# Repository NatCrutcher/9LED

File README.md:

## Overview

This is a small test PCB to experiment with wide color gamut LEDs. The initial plan is to use the following LEDs, driven by the TI TLC5971 (high-quality 16-bit PWM).

1. Violet 410 (XE-G)
2. Blue PC 460 (OSLON)
3. Cyan 500 (XE-G)
4. Green 525 (OSLON)
5. Yellow PC 590 (OSLON)
6. Red 620 (OSLON)
7. Photo Red 660 (XE-G)
8. Far Red 735 (Luxeon)
9. White (OSLON)

This should allow tests to compare more traditional RGB and RGBW color gamuts to wider gamuts. In particular, deeper reds, violet, and cyan. 

### Cyan
Initial testing shows that the cyan LED makes a color that is perceptually different from just mixing various amounts of green and blue. Green+blue results in the traditional computer monitor "cyan", which is really more turquoise. The pure cyan LED results in a more saturated (computer monitor cyan is a bit pastel by comparison) strong green-blue color.

### Violet

By itself, the violet LED is not what I expected: it seems almost like a purple/blue/white mixture. I need to do more research to make sure it is not exciting the phosphors in the white LED (perhaps build a board without the white). My plans are to compare purples (red+blue and red+violet) to see if violet generates noticeably different (i.e. more intense) purpl

### Photo Red and Far Red

This is an interesting example of how our eyes acclimate, color balance, and otherwise shift our perceptions. When I look at the normal red LED, it looks strongly red. But when I look at normal red next to photo red, the photo red looks more intensely red and the normal red starts to look like an orange-red. I want to try a larger experiment to determine how this effect scales.

The far red appears to be useless for LED sculptures, animations, or lighting. The perceived brightness is MUCH (like 10-20X) lower, so it can only produce very dim illumination. And as seen on the chromaticity diagrams, the perceived color is very close to photo red, so it does not meaningfully increase the gamut.

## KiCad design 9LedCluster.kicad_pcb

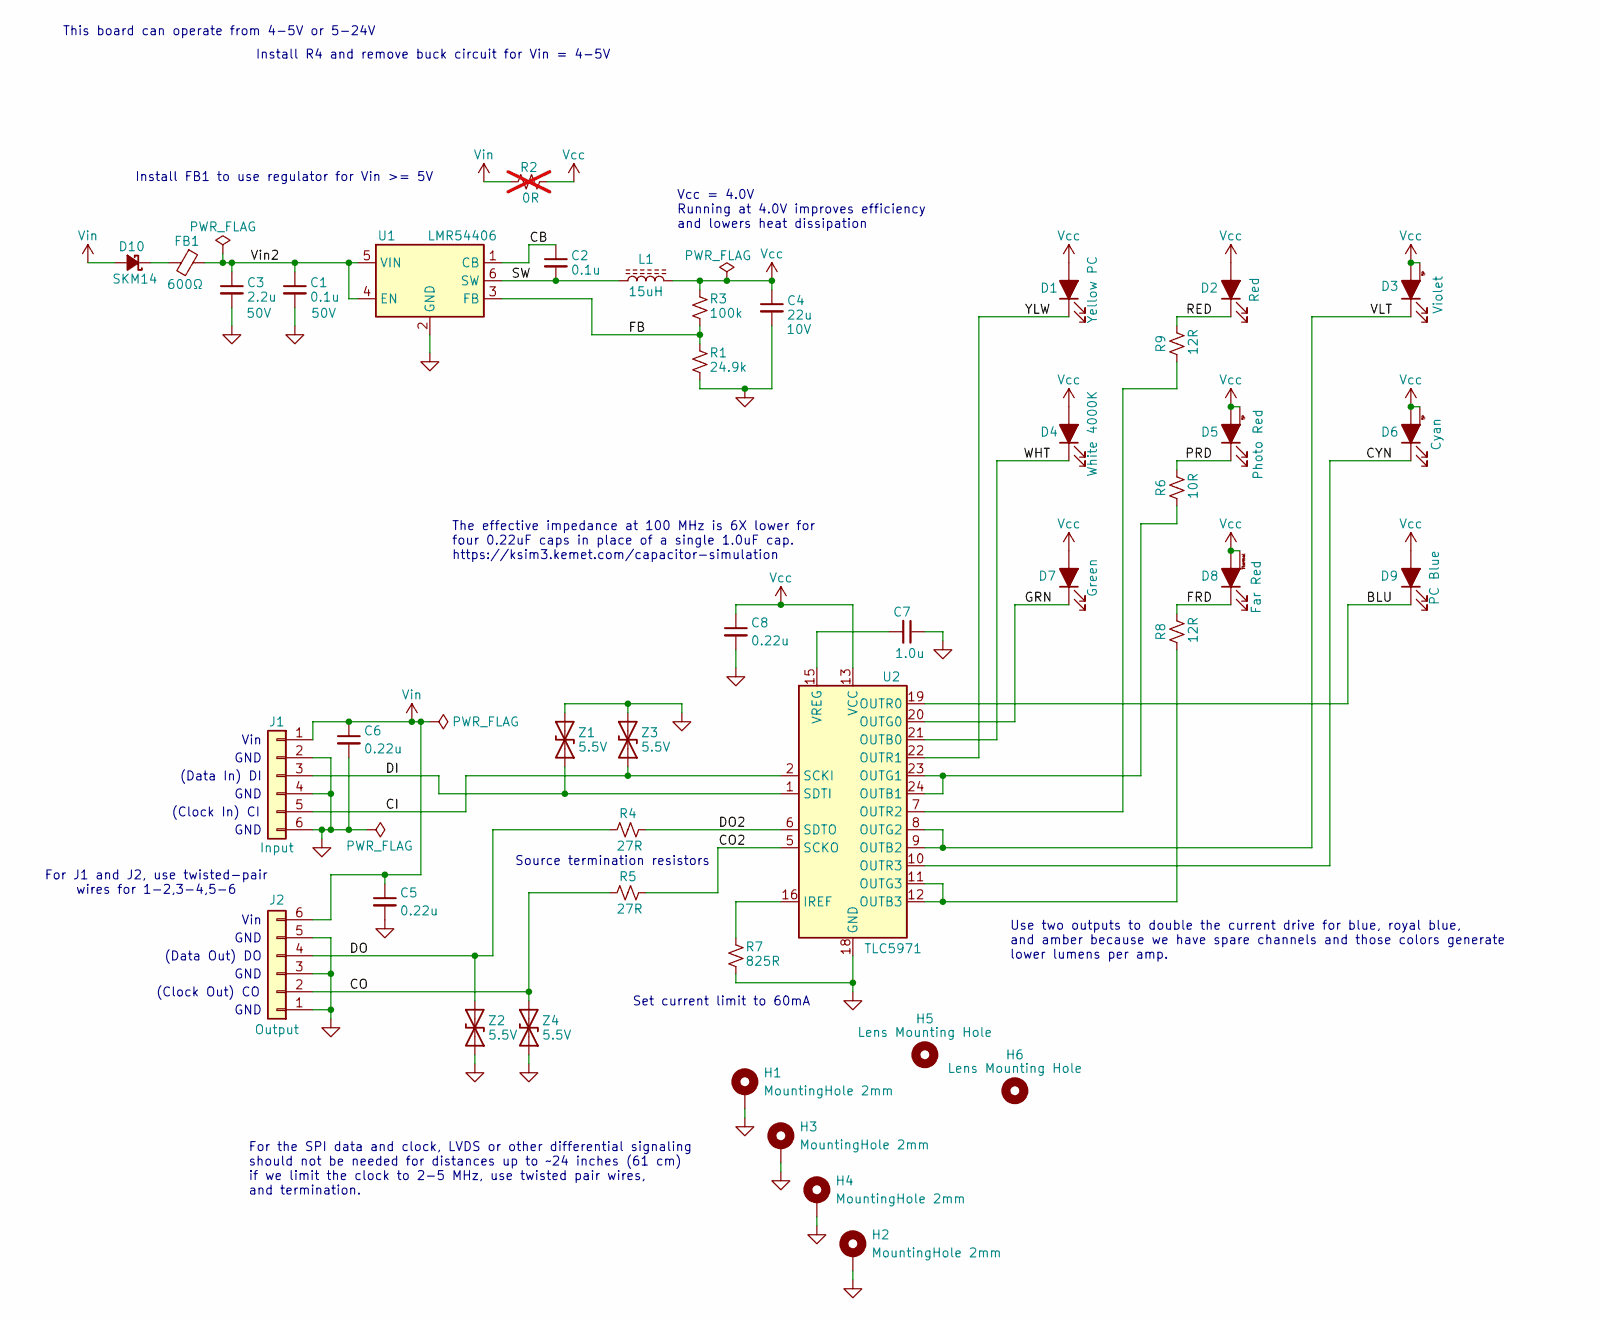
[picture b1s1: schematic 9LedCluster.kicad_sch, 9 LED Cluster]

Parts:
C1, C2: 0.1u; C_0402_1005Metric; Rating 50V; Tolerance 10%; MPN GRM155R71H104KE14D
C3: 2.2u; C_0805_2012Metric; Rating 50V; Tolerance 10%; MPN UMK212BB7225KG-T
C4: 22u; C_0805_2012Metric; Rating 10V; Tolerance 20%; MPN GRM21BZ71A226ME15L
C5, C6, C8: 0.22u; C_0402_1005Metric; Rating 16V; Tolerance 20%; MPN C0402C224M4RACTU
C7: 1.0u; C_0603_1608Metric; Rating 25V; Tolerance 10%; MPN TMK107B7105KA-T
D1: Yellow PC; OSRAM-OSLON-Pure-1414; Rating 350mA; MPN GY VJLPL1.F3-KULQ-YCYK-1
D2: Red; OSRAM-OSLON-Pure-1414; Rating 350mA; MPN GR VJLPL1.23-KQKS-A4R2-1
D3: Violet; Cree_XE-G; Rating 1A; MPN XEGAVT-H0-0000-000-000000K2001
D4: White 4000K; OSRAM-OSLON-Pure-1414; Rating 350mA; MPN GW VJLPL1.CM-K3LX-XX55-1
D5: Photo Red; Cree_XE-G; Rating 1A; MPN XEGAHR-H2-0000-000-000000H6001
D6: Cyan; Cree_XE-G; Rating 1A; MPN XEGACY-H2-0000-000-000000T3001
D7: Green; OSRAM-OSLON-Pure-1414; Rating 350mA; MPN GT VJLPL1.13-LPLS-T3T4-1
D8: Far Red; Luxeon_CZ_LED_AK; Rating 350mA; MPN L1C1-FRD1000000000
D9: PC Blue; OSRAM-OSLON-Pure-1414; Rating 350mA; MPN GB VJLPL1.F3-JRJT-BABB-1
D10: SKM14; D_SOD-123F; Rating 40V, 1A; Rating2 350mV @ 1A; MPN SKM14
FB1: 600Ω; R_0603_1608Metric_Pad0.98x0.95mm_HandSolder; Rating 1.3A; Rating2 DCR=150mΩ; MPN BLM18KG601SN1D
H1, H2, H3, H4: MountingHole 2mm; MountingHole_2.0mm_A
H5, H6: Lens Mounting Hole; MountingHole_2.0mm_NP
J1: Input; Conn_2.00mm_6_LED
J2: Output; Conn_2.00mm_6_LED
L1: 15uH; L_1210_3225Metric; Rating I=1.47; Rating2 320 mOhm Max; MPN BCL322520RT-150M-D
R1: 24.9k; R_0603_1608Metric; Tolerance 0.5%; Rating 0.063W; MPN RR0816P-2492-D-39C
R2: 0R; R_0402_1005Metric; Tolerance jumper; MPN RK73Z1ETTP; not fitted
R3: 100k; R_0603_1608Metric; Tolerance 0.5%; Rating 0.1W; MPN RT0603DRD07100KL
R4, R5: 27R; R_0402_1005Metric; Tolerance 1%; Rating 0.063W; MPN RT0402FRE0727RL
R6: 10R; R_0603_1608Metric; Tolerance 1%; Rating 0.125W; MPN RK73H1JTTD10R0F
R7: 825R; R_0402_1005Metric; Tolerance 1%; Rating 0.063W; MPN RR0510P-8250-D
R8, R9: 12R; R_0603_1608Metric; Tolerance 1%; Rating 0.125W; MPN RK73H1JTTD12R0F
U1: LMR54406; SOT-23-6; Rating 1.1MHz; Rating2 600mA; MPN LMR54406DBVR
U2: TLC5971; Texas_RGE0024H_VQFN-24-1EP_4x4mm_P0.5mm_EP2.7x2.7mm_Thermal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; Rating 17V, 60mA; Rating2 12ch, 16bit; MPN TLC5971RGER
Z1, Z2, Z3, Z4: 5.5V; R_0402_1005Metric; Rating 5.5V, 10pF; Rating2 25kV ESD; MPN GG040205100N2P

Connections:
/BLU: D9.K, U2.19 (OUTR0)
/CB: C2.1, U1.1 (CB)
/CI: J1.5, U2.2 (SCKI), Z3.1 (A1)
/CO: J2.2, R5.1, Z4.2 (A2)
/CO2: R5.2, U2.5 (SCKO)
/CYN: D6.K, U2.10 (OUTR3)
/DI: J1.3, U2.1 (SDTI), Z1.1 (A1)
/DO: J2.4, R4.1, Z2.2 (A2)
/DO2: R4.2, U2.6 (SDTO)
/FB: R1.1, R3.2, U1.3 (FB)
/FRD: D8.K, R8.2
/GRN: D7.K, U2.20 (OUTG0)
/PRD: D5.K, R6.2
/RED: D2.K, R9.2
/SW: C2.2, L1.1, U1.6 (SW)
/VLT: D3.K, U2.8 (OUTG2), U2.9 (OUTB2)
/Vin2: C1.1, C3.1, FB1.1, U1.4 (EN), U1.5 (VIN)
/WHT: D4.K, U2.21 (OUTB0)
/YLW: D1.K, U2.22 (OUTR1)
GND: C1.2, C3.2, C4.2, C5.2, C6.2, C7.1, C8.2, H1.1, H2.1, H3.1, H4.1, J1.2, J1.4, J1.6, J2.1, J2.3, J2.5, R1.2, R7.2, U1.2 (GND), U2.18 (GND), U2.25 (GND), Z1.2 (A2), Z2.1 (A1), Z3.2 (A2), Z4.1 (A1)
unnamed: D10.1 (K), FB1.2
unnamed: R7.1, U2.16 (IREF)
unnamed: R6.1, U2.23 (OUTG1), U2.24 (OUTB1)
unnamed: R8.1, U2.11 (OUTG3), U2.12 (OUTB3)
unnamed: R9.1, U2.7 (OUTR2)
unnamed: C7.2, U2.15 (VREG)
Vcc: C4.1, C8.1, D1.A, D2.A, D3.A, D3.TP, D4.A, D5.A, D5.TP, D6.A, D6.TP, D7.A, D8.A, D8.TP, D9.A, L1.2, R2.2, R3.1, U2.13 (VCC)
Vin: C5.1, C6.1, D10.2 (A), J1.1, J2.6, R2.1

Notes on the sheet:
(Clock In) CI
(Data Out) DO
Vin
GND
For the SPI data and clock, LVDS or other differential signaling should not be needed for distances up to ~24 inches (61 cm) if we limit the clock to 2-5 MHz, use twisted pair wires, and termination.
Use two outputs to double the current drive for blue, royal blue, and amber because we have spare channels and those colors generate lower lumens per amp.
Install FB1 to use regulator for Vin >= 5V
This board can operate from 4-5V or 5-24V
For J1 and J2, use twisted-pair wires for 1-2,3-4,5-6
Source termination resistors
The effective impedance at 100 MHz is 6X lower for four 0.22uF caps in place of a single 1.0uF cap. https://ksim3.kemet.com/capacitor-simulation
Install R4 and remove buck circuit for Vin = 4-5V
(Data In) DI
(Clock Out) CO
Vcc = 4.0V Running at 4.0V improves efficiency and lowers heat dissipation
Set current limit to 60mA

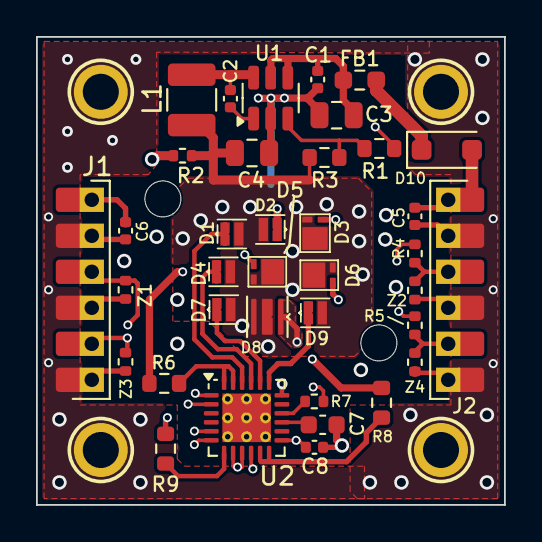
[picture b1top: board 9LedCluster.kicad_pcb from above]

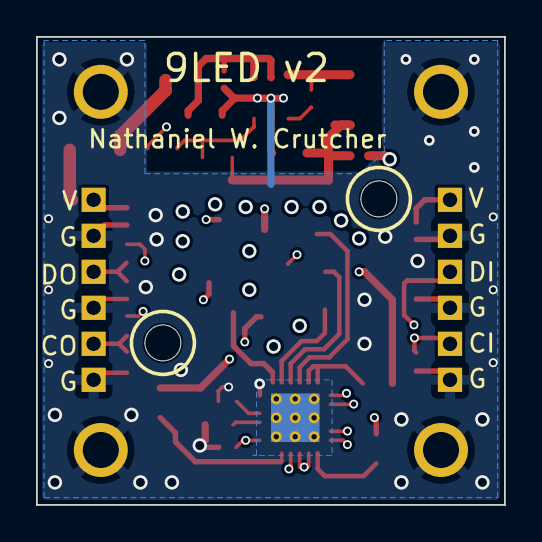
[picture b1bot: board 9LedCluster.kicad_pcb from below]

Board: 4 copper layers, 26.0 x 26.0 mm, 45 parts (2 on the bottom side), 28 nets.

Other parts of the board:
FID1, FID2: Fiducial_0402_Pad
